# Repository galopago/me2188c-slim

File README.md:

# ME2188 Step-Up Module

This is a small step-up module based on the  chip, designed specifically for low-power 3.3V embedded systems. It allows you to boost the voltage from a single 1.5V battery to 3.3V, enabling you to power your projects efficiently.

## Features

- Compact size: 15.7mm x 15.7mm
- Designed for low-power 3.3V embedded systems
- All components on the front PCB layer
- External pins spaced 2.54mm for easy integration
- Input voltage: 1.5V (single battery)

## Module Images

Here you can find images of the finished module and the panelized PCB. These images will help you visualize the module's physical appearance and layout.

## License

This project is licensed under the [MIT License](LICENSE).

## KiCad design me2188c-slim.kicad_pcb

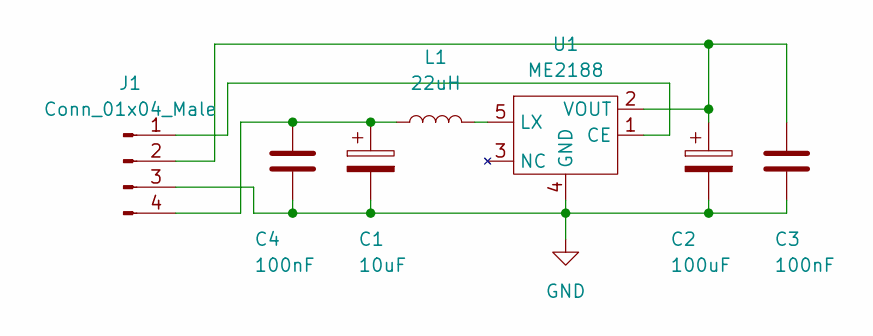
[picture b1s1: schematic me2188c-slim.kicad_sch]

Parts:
C1: 10uF; CP_EIA-7343-31_Kemet-D_Pad2.25x2.55mm_HandSolder
C2: 100uF; CP_EIA-7343-31_Kemet-D_Pad2.25x2.55mm_HandSolder
C3, C4: 100nF; C_0805_2012Metric_Pad1.18x1.45mm_HandSolder
J1: Conn_01x04_Male; PinHeader_1x04_P2.54mm_Vertical
L1: 22uH; L_Ferrocore_DLG-0403
U1: ME2188; SOT-23-5_HandSoldering

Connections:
GND: C1.2, C2.2, C3.2, C4.2, J1.3, U1.4 (GND)
unnamed: C1.1, C4.1, J1.4, L1.1
unnamed: C2.1, C3.1, J1.2, U1.2 (VOUT)
unnamed: L1.2, U1.5 (LX)
unnamed: J1.1, U1.1 (CE)

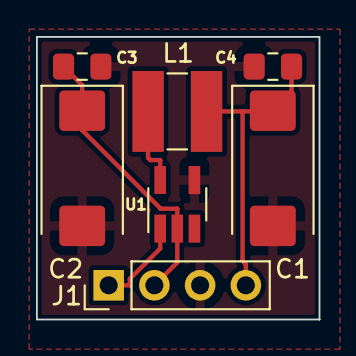
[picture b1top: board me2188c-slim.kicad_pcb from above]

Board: 2 copper layers, 15.7 x 15.7 mm, 7 parts (0 on the bottom side), 5 nets.

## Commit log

2023-04-03 started PCB
2023-04-04 routed
2023-04-11 pdf added
2023-04-11 pdf added cd43 coil
2023-04-14 inductor footprint corrected and capacitors added
2023-04-17 board routed
2023-04-17 shrinked and routed
2023-04-18 finished
2023-04-18 OSHW logo added
2023-04-18 single gerber
2023-05-22 panel gerbers added
2023-05-23 started readme
2023-05-28 some pics added
2023-05-28 some pics added+
